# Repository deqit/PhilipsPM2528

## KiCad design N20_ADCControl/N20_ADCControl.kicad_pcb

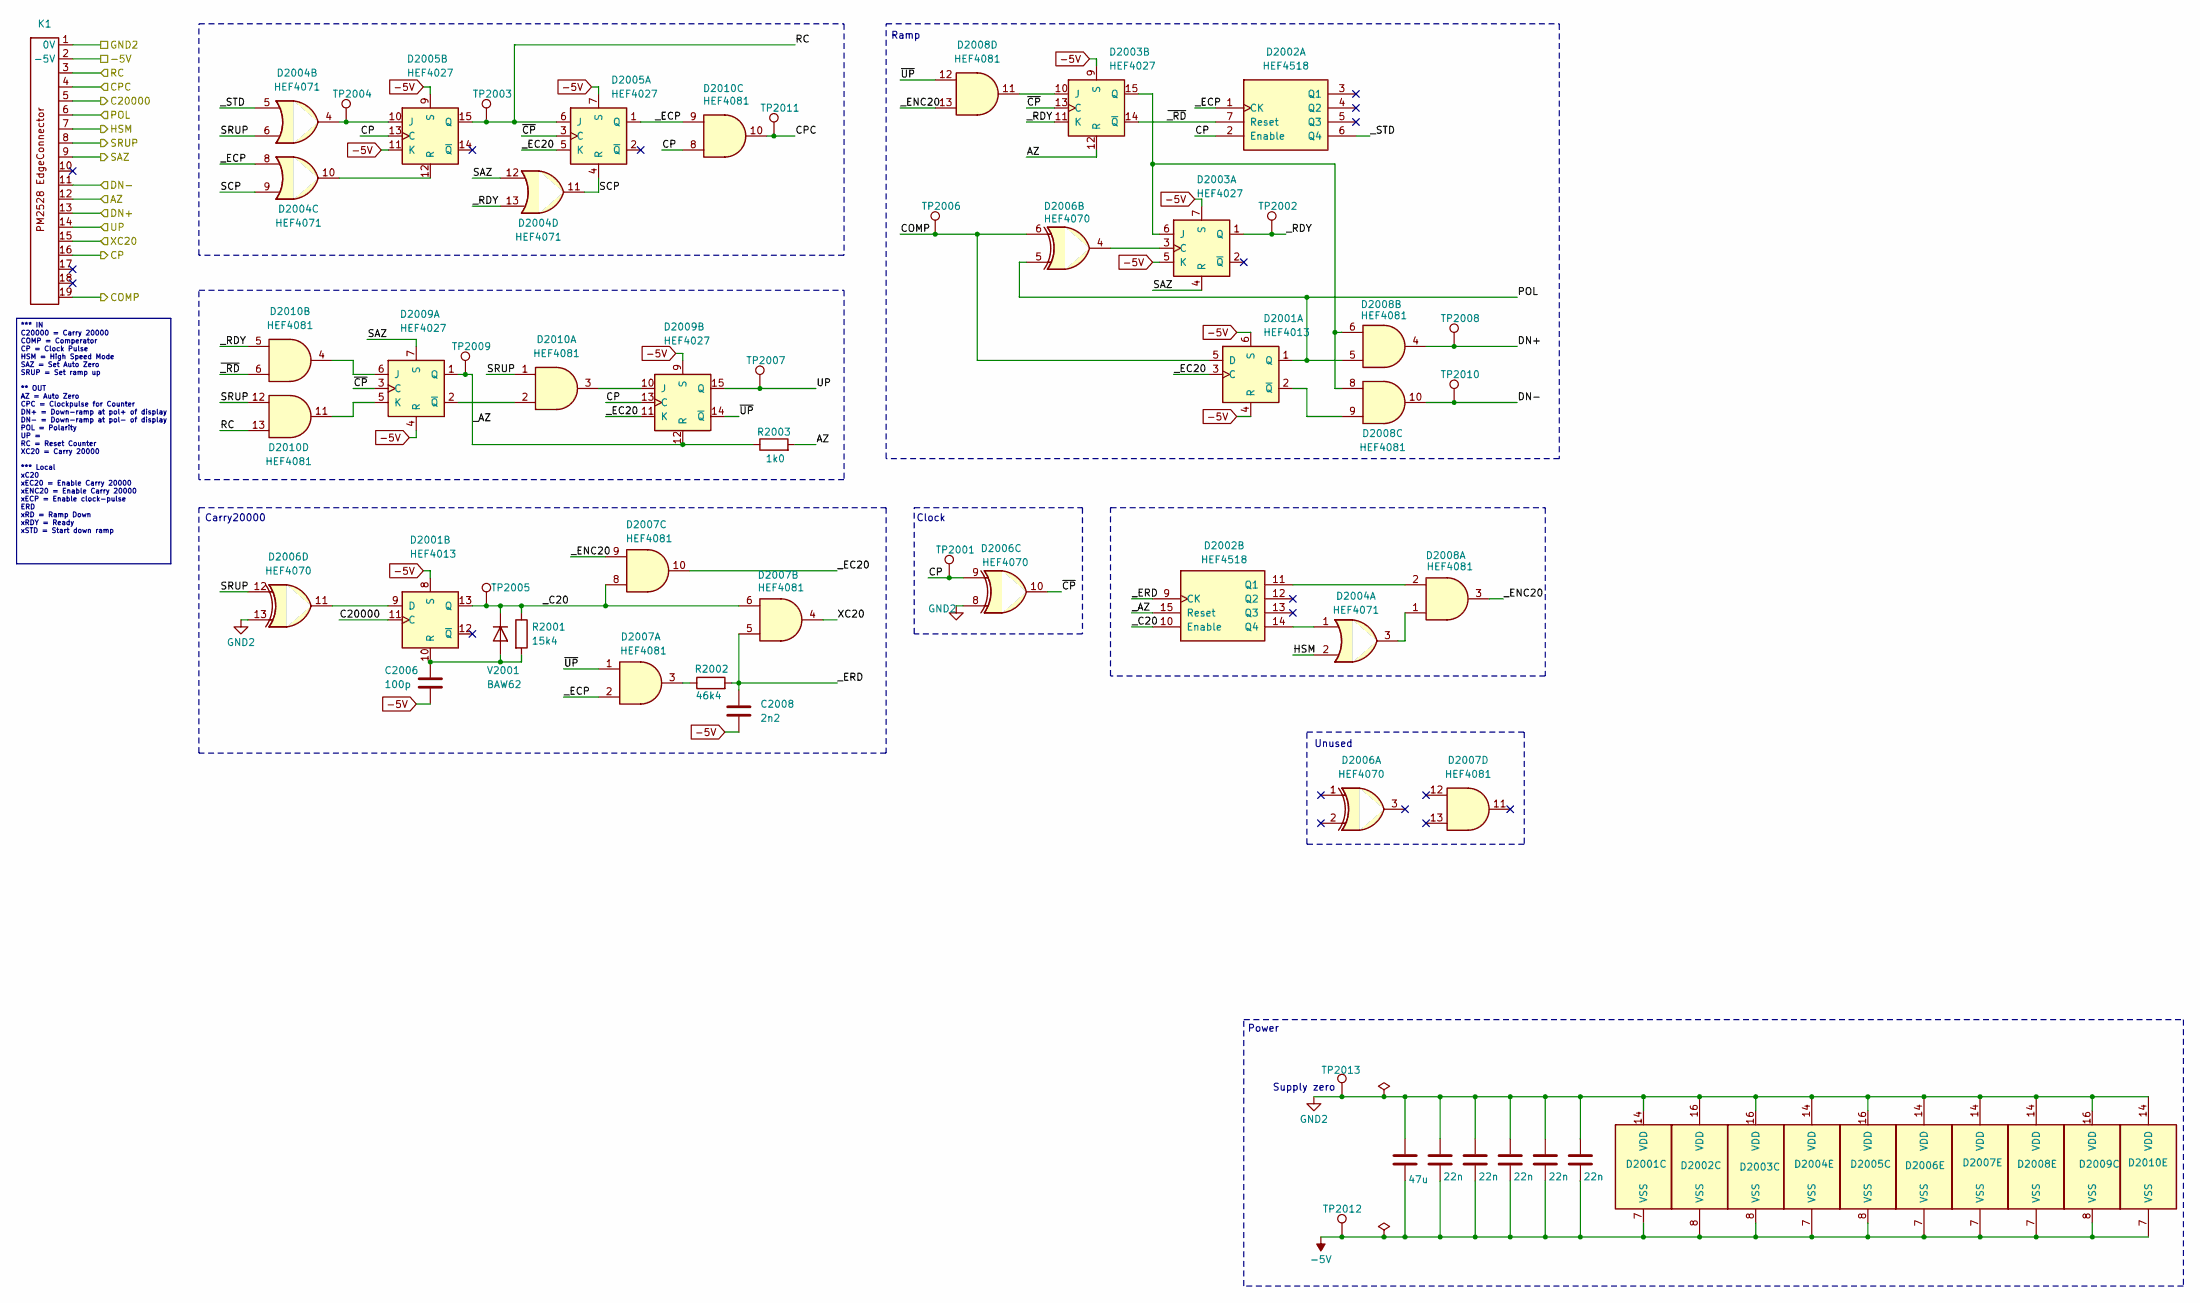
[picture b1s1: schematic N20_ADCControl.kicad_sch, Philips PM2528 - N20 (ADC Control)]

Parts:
C2001, C2002, C2003, C2004, C2005: 22n; C_Rect_L7.0mm_W2.0mm_P5.00mm
C2006: 100p; C_Rect_L7.0mm_W2.0mm_P5.00mm
C2007: 47u; CP_Axial_L10.0mm_D6.0mm_P15.00mm_Horizontal
C2008: 2n2; C_Rect_L7.0mm_W2.0mm_P5.00mm
D2001: HEF4013; DIP-14_W7.62mm
D2002: HEF4518; DIP-16_W7.62mm
D2003, D2005, D2009: HEF4027; DIP-16_W7.62mm
D2004: HEF4071; DIP-14_W7.62mm
D2006: HEF4070; DIP-14_W7.62mm
D2007, D2008, D2010: HEF4081; DIP-14_W7.62mm
K1: PM2528_RiserCardConnector
R2001: 15k4; R_Axial_DIN0207_L6.3mm_D2.5mm_P10.16mm_Horizontal
R2002: 46k4; R_Axial_DIN0207_L6.3mm_D2.5mm_P10.16mm_Horizontal
R2003: 1k0; R_Axial_DIN0207_L6.3mm_D2.5mm_P10.16mm_Horizontal
TP2001, TP2002, TP2003, TP2004, TP2005, TP2006, TP2007, TP2008, TP2009, TP2010, TP2011, TP2012, TP2013: TestPoint; PinHeader_1x01_P1.00mm_Vertical
V2001: BAW62; D_T-1_P10.16mm_Horizontal

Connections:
-5V: C2001.2, C2002.2, C2003.2, C2004.2, C2005.2, C2006.2, C2007.2, C2008.2, D2001.4 (R), D2001.6 (S), D2001.7 (VSS), D2001.8 (S), D2002.8 (VSS), D2003.5 (K), D2003.7 (S), D2003.8 (VSS), D2003.9 (S), D2004.7 (VSS), D2005.7 (S), D2005.8 (VSS), D2005.9 (S), D2005.11 (K), D2006.7 (VSS), D2007.7 (VSS), D2008.7 (VSS), D2009.4 (R), D2009.8 (VSS), D2009.9 (S), D2010.7 (VSS), K1.2 (-5V), TP2012.1
/AZ: D2003.12 (R), K1.12, R2003.2
/C20000: D2001.11 (C), K1.5
/COMP: D2001.5 (D), D2006.6, K1.19, TP2006.1
/CP: D2002.2 (Enable), D2005.13 (C), D2006.9, D2009.13 (C), D2010.8, K1.16, TP2001.1
/CPC: D2010.10, K1.4, TP2011.1
/DN+: D2008.4, K1.13, TP2008.1
/DN-: D2008.10, K1.11, TP2010.1
/HSM: D2004.2, K1.7
/POL: D2001.1 (Q), D2006.5, D2008.5, K1.6
/RC: D2005.6 (J), D2005.15 (Q), D2010.13, K1.3, TP2003.1
/SAZ: D2003.4 (R), D2004.12, D2009.7 (S), K1.9
/SCP: D2004.9, D2004.11, D2005.4 (R)
/SRUP: D2004.6, D2006.12, D2010.1, D2010.12, K1.8
/UP: D2009.15 (Q), K1.14, TP2007.1
/XC20: D2007.4, K1.15
/_AZ: D2002.15 (Reset), D2009.1 (Q), D2009.12 (R), R2003.1, TP2009.1
/_C20: D2001.13 (Q), D2002.10 (Enable), D2007.6, D2007.8, R2001.1, TP2005.1, V2001.1 (K)
/_EC20: D2001.3 (C), D2005.5 (K), D2007.10, D2009.11 (K)
/_ECP: D2002.1 (CK), D2004.8, D2005.1 (Q), D2007.2, D2010.9
/_ENC20: D2007.9, D2008.3, D2008.13
/_ERD: C2008.1, D2002.9 (CK), D2007.5, R2002.2
/_RDY: D2003.1 (Q), D2003.11 (K), D2004.13, D2010.5, TP2002.1
/_STD: D2002.6 (Q4), D2004.5
/~CP: D2003.13 (C), D2005.3 (C), D2006.10, D2009.3 (C)
/~UP: D2007.1, D2008.12, D2009.14 (~Q)
/~_RD: D2002.7 (Reset), D2003.14 (~Q), D2010.6
GND2: C2001.1, C2002.1, C2003.1, C2004.1, C2005.1, C2007.1, D2001.14 (VDD), D2002.16 (VDD), D2003.16 (VDD), D2004.14 (VDD), D2005.16 (VDD), D2006.8, D2006.13, D2006.14 (VDD), D2007.14 (VDD), D2008.14 (VDD), D2009.16 (VDD), D2010.14 (VDD), K1.1 (0V), TP2013.1
unnamed: D2001.2 (~Q), D2008.9
unnamed: D2001.9 (D), D2006.11
unnamed: C2006.1, D2001.10 (R), R2001.2, V2001.2 (A)
unnamed: D2002.11 (Q1), D2008.2
unnamed: D2002.14 (Q4), D2004.1
unnamed: D2003.3 (C), D2006.4
unnamed: D2003.6 (J), D2003.15 (Q), D2008.6, D2008.8
unnamed: D2003.10 (J), D2008.11
unnamed: D2004.3, D2008.1
unnamed: D2004.4, D2005.10 (J), TP2004.1
unnamed: D2004.10, D2005.12 (R)
unnamed: D2007.3, R2002.1
unnamed: D2009.6 (J), D2010.4
unnamed: D2009.5 (K), D2010.11
unnamed: D2009.2 (~Q), D2010.2
unnamed: D2009.10 (J), D2010.3

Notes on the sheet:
Ramp
Power
Supply zero
Clock
Carry20000
Unused
*** IN C20000 = Carry 20000 COMP = Comperator CP = Clock Pulse HSM = High Speed Mode SAZ = Set Auto Zero SRUP = Set ramp up ** OUT AZ = Auto Zero CPC = Clockpulse for Counter DN+ = Down-ramp at pol+ of display DN- = Down-ramp at pol- of display POL = Polarity UP = RC = Reset Counter XC20 = Carry 20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

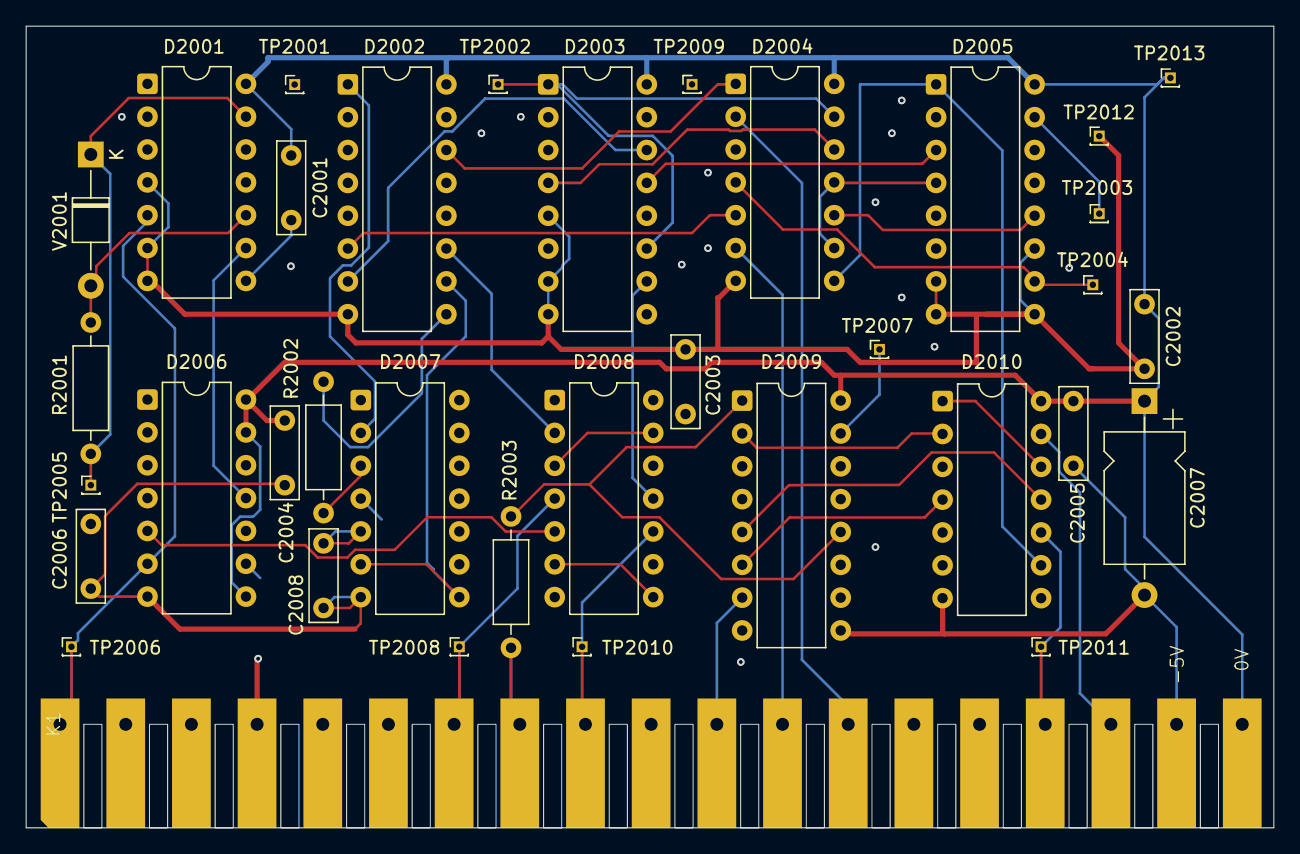
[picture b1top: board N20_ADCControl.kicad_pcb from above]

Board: 2 copper layers, 96.5 x 62.0 mm, 36 parts (0 on the bottom side), 44 nets.

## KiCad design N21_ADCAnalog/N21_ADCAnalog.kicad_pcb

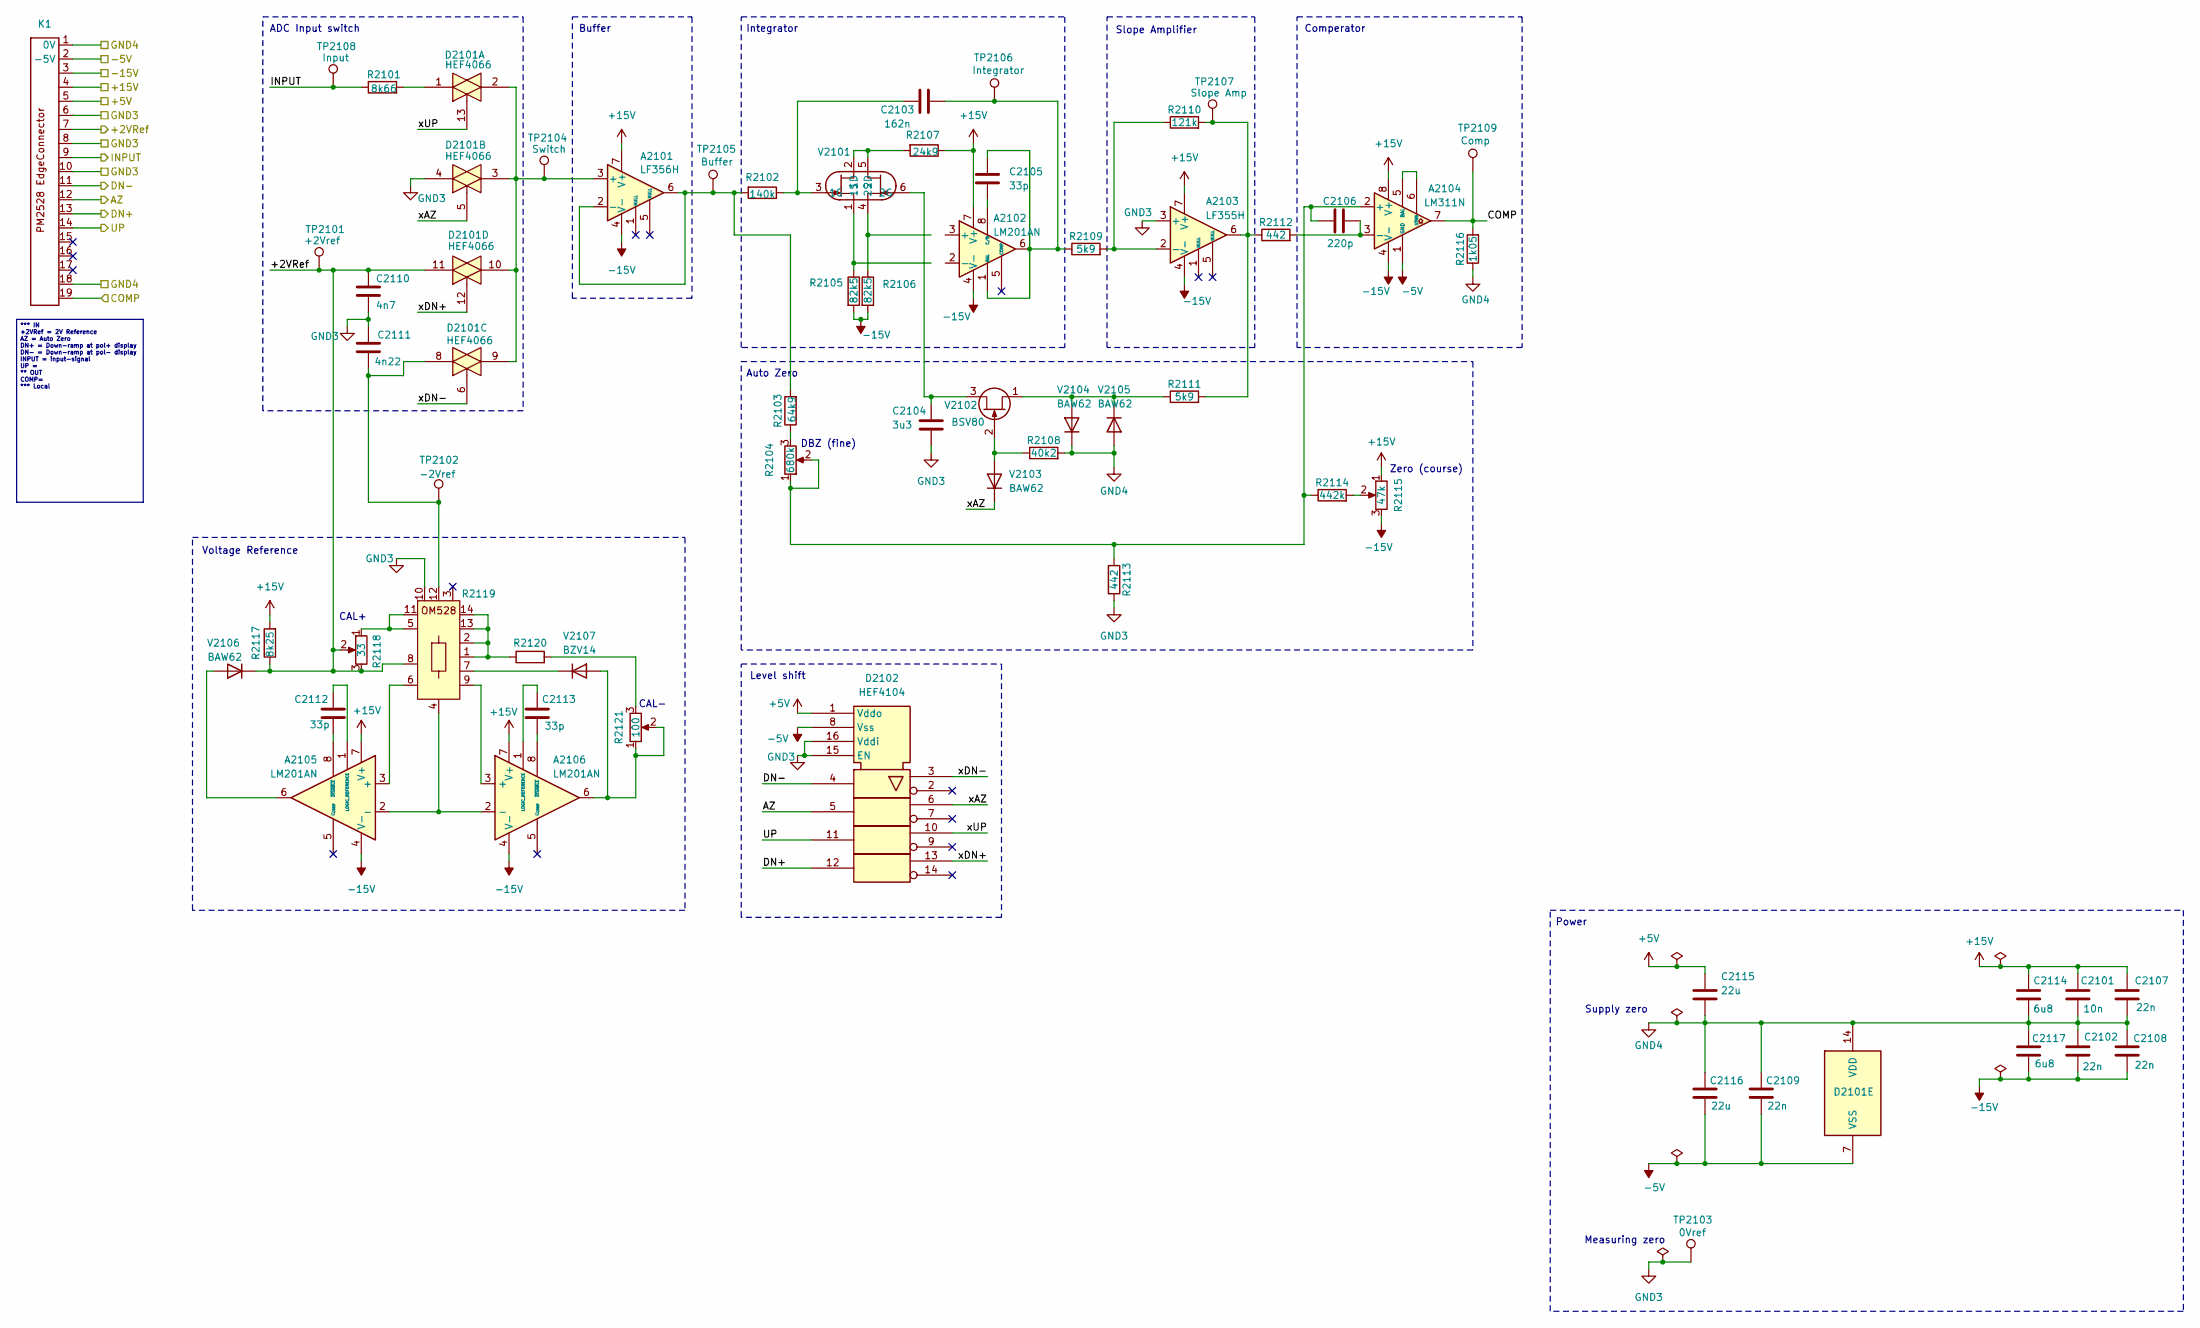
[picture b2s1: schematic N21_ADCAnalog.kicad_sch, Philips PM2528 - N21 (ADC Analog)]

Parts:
A2101: LF356H; DIP-8_W7.62mm
A2102, A2105, A2106: LM201AN; DIP-8_W7.62mm
A2103: LF355H; DIP-8_W7.62mm
A2104: LM311N
C2101: 10n; C_Disc_D4.3mm_W1.9mm_P5.00mm
C2102, C2107, C2108, C2109: 22n; C_Disc_D4.3mm_W1.9mm_P5.00mm
C2103: 162n; CP_Axial_L25.0mm_D10.0mm_P30.00mm_Horizontal
C2104: 3u3; C_Rect_L26.5mm_W8.5mm_P22.50mm_MKS4
C2105, C2112, C2113: 33p; C_Disc_D4.3mm_W1.9mm_P5.00mm
C2106: 220p; C_Disc_D4.3mm_W1.9mm_P5.00mm
C2110: 4n7; C_Disc_D4.3mm_W1.9mm_P5.00mm
C2111: 4n22
C2114, C2117: 6u8; C_Disc_D5.0mm_W2.5mm_P5.00mm
C2115, C2116: 22u; C_Disc_D5.0mm_W2.5mm_P5.00mm
D2101: HEF4066; DIP-14_W7.62mm
D2102: HEF4104; DIP-16_W7.62mm
K1: PM2528_RiserCardConnector
R2101: 8k66; R_Axial_DIN0207_L6.3mm_D2.5mm_P10.16mm_Horizontal
R2102: 140k; R_Axial_DIN0207_L6.3mm_D2.5mm_P10.16mm_Horizontal
R2103: 64k9; R_Axial_DIN0207_L6.3mm_D2.5mm_P10.16mm_Horizontal
R2104: 680k; Potentiometer horizontal ceramic
R2105, R2106: 82k5; R_Axial_DIN0207_L6.3mm_D2.5mm_P10.16mm_Horizontal
R2107: 24k9; R_Axial_DIN0207_L6.3mm_D2.5mm_P10.16mm_Horizontal
R2108: 40k2; R_Axial_DIN0207_L6.3mm_D2.5mm_P10.16mm_Horizontal
R2109, R2111: 5k9; R_Axial_DIN0207_L6.3mm_D2.5mm_P10.16mm_Horizontal
R2110: 121k; R_Axial_DIN0207_L6.3mm_D2.5mm_P10.16mm_Horizontal
R2112, R2113: 442; R_Axial_DIN0207_L6.3mm_D2.5mm_P10.16mm_Horizontal
R2114: 442k; R_Axial_DIN0207_L6.3mm_D2.5mm_P10.16mm_Horizontal
R2115: 47k; Potentiometer horizontal ceramic
R2116: 1k05; R_Axial_DIN0207_L6.3mm_D2.5mm_P10.16mm_Horizontal
R2117: 8k25; R_Axial_DIN0207_L6.3mm_D2.5mm_P10.16mm_Horizontal
R2118: 33; Potentiometer horizontal ceramic
R2119: DIP-14_W7.62mm_Socket
R2120: (no value)
R2121: 100; Potentiometer horizontal ceramic
TP2101: +2Vref; Pin_D1.0mm_L10.0mm
TP2102: -2Vref; Pin_D1.0mm_L10.0mm
TP2103: 0Vref; Pin_D1.0mm_L10.0mm
TP2104: Switch; Pin_D1.0mm_L10.0mm
TP2105: Buffer; Pin_D1.0mm_L10.0mm
TP2106: Integrator; Pin_D1.0mm_L10.0mm
TP2107: Slope Amp; Pin_D1.0mm_L10.0mm
TP2108: Input; Pin_D1.0mm_L10.0mm
TP2109: Comp; Pin_D1.0mm_L10.0mm
V2101: (no value)
V2102: BSV80; TO-92_Inline
V2103, V2104, V2105, V2106: BAW62; D_DO-34_SOD68_P10.16mm_Horizontal
V2107: BZV14; D_DO-34_SOD68_P10.16mm_Horizontal

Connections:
+5V: C2115.1, D2102.1 (Vddo), K1.5
+15V: A2101.7 (V+), A2102.7 (V+), A2103.7 (V+), A2104.8 (V+), A2105.7 (V+), A2106.7 (V+), C2101.2, C2107.1, C2114.1, K1.4, R2107.1, R2115.1, R2117.2
-5V: A2104.1 (GND), C2109.2, C2116.2, D2101.7 (VSS), D2102.8 (Vss), K1.2 (-5V)
-15V: A2101.4 (V-), A2102.4 (V-), A2103.4 (V-), A2104.4 (V-), A2105.4 (V-), A2106.4 (V-), C2102.2, C2108.2, C2117.2, K1.3, R2105.2, R2106.2, R2115.3
/+2VRef: C2110.2, D2101.11, K1.7, R2117.1, R2118.2, R2118.3, R2119.8, TP2101.1, V2106.1 (K)
/AZ: D2102.5, K1.12
/COMP: A2104.7, K1.19, R2116.2, TP2109.1
/DN+: D2102.12, K1.13
/DN-: D2102.4, K1.11
/INPUT: K1.9, R2101.1, TP2108.1
/UP: D2102.11, K1.14
/xAZ: D2101.5, D2102.6, V2103.1 (K)
/xDN+: D2101.12, D2102.13
/xDN-: D2101.6, D2102.3
/xUP: D2101.13, D2102.10
GND3: A2103.3 (+), C2104.2, C2110.1, C2111.2, D2101.4, D2102.15 (EN), D2102.16 (Vddi), K1.6, K1.8, K1.10, R2113.2, R2119.10, TP2103.1
GND4: C2101.1, C2102.1, C2107.2, C2108.1, C2109.1, C2114.2, C2115.2, C2116.1, C2117.1, D2101.14 (VDD), K1.1 (0V), K1.18, R2108.2, R2116.1, V2104.1 (K), V2105.2 (A)
unnamed: A2101.3 (+), D2101.2, D2101.3, D2101.9, D2101.10, TP2104.1
unnamed: A2101.2 (-), A2101.6, R2102.2, R2103.2, TP2105.1
unnamed: A2102.1 (BAL), A2102.6, C2103.1, C2105.1, R2109.1, TP2106.1
unnamed: A2102.8 (C/B), C2105.2
unnamed: A2103.2 (-), R2109.2, R2110.1
unnamed: A2103.6, R2110.2, R2111.2, R2112.1, TP2107.1
unnamed: A2104.2 (+), C2106.2, R2104.1, R2104.2, R2113.1, R2114.1
unnamed: A2104.3 (-), C2106.1, R2112.2
unnamed: A2104.5 (BAL), A2104.6 (STRB)
unnamed: A2105.3 (+), R2119.6
unnamed: A2105.2 (-), A2106.2 (-), R2119.4
unnamed: A2105.1 (LOGIC_REFERENCE), C2112.2
unnamed: A2105.8 (~DISABLE), C2112.1
unnamed: A2106.3 (+), R2119.9
unnamed: A2106.1 (LOGIC_REFERENCE), C2113.2
unnamed: A2106.8 (~DISABLE), C2113.1
unnamed: C2111.1, D2101.8, R2119.12, TP2102.1
unnamed: D2101.1, R2101.2
unnamed: R2103.1, R2104.3
unnamed: R2114.2, R2115.2
unnamed: R2118.1, R2119.5, R2119.11
unnamed: R2119.1, R2119.2, R2119.13, R2119.14, R2120.1
unnamed: R2120.2, R2121.3
unnamed: R2107.2, V2101.2 (1D), V2101.5 (2D)
unnamed: C2103.2, R2102.1, V2101.3 (1G)
unnamed: R2105.1, V2101.1 (1S)
unnamed: C2104.1, V2101.6 (2G), V2102.3 (S)
unnamed: R2106.1, V2101.4 (2S)
unnamed: R2111.1, V2102.1 (D), V2104.2 (A), V2105.1 (K)
unnamed: R2108.1, V2102.2 (G), V2103.2 (A)
unnamed: A2105.6, V2106.2 (A)
unnamed: A2106.6, R2121.1, R2121.2, V2107.2 (A)
unnamed: R2119.7, V2107.1 (K)

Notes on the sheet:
Supply zero
CAL+
Buffer
Power
Comperator
Voltage Reference
Integrator
DBZ (fine)
Measuring zero
Slope Amplifier
Zero (course)
Auto Zero
Level shift
CAL-
ADC Input switch
*** IN +2VRef = 2V Reference AZ = Auto Zero DN+ = Down-ramp at pol+ display DN- = Down-ramp at pol- display INPUT = input-signal UP = ** OUT COMP= *** Local

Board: 2 copper layers, 60 parts (0 on the bottom side), 46 nets, no tracks yet.

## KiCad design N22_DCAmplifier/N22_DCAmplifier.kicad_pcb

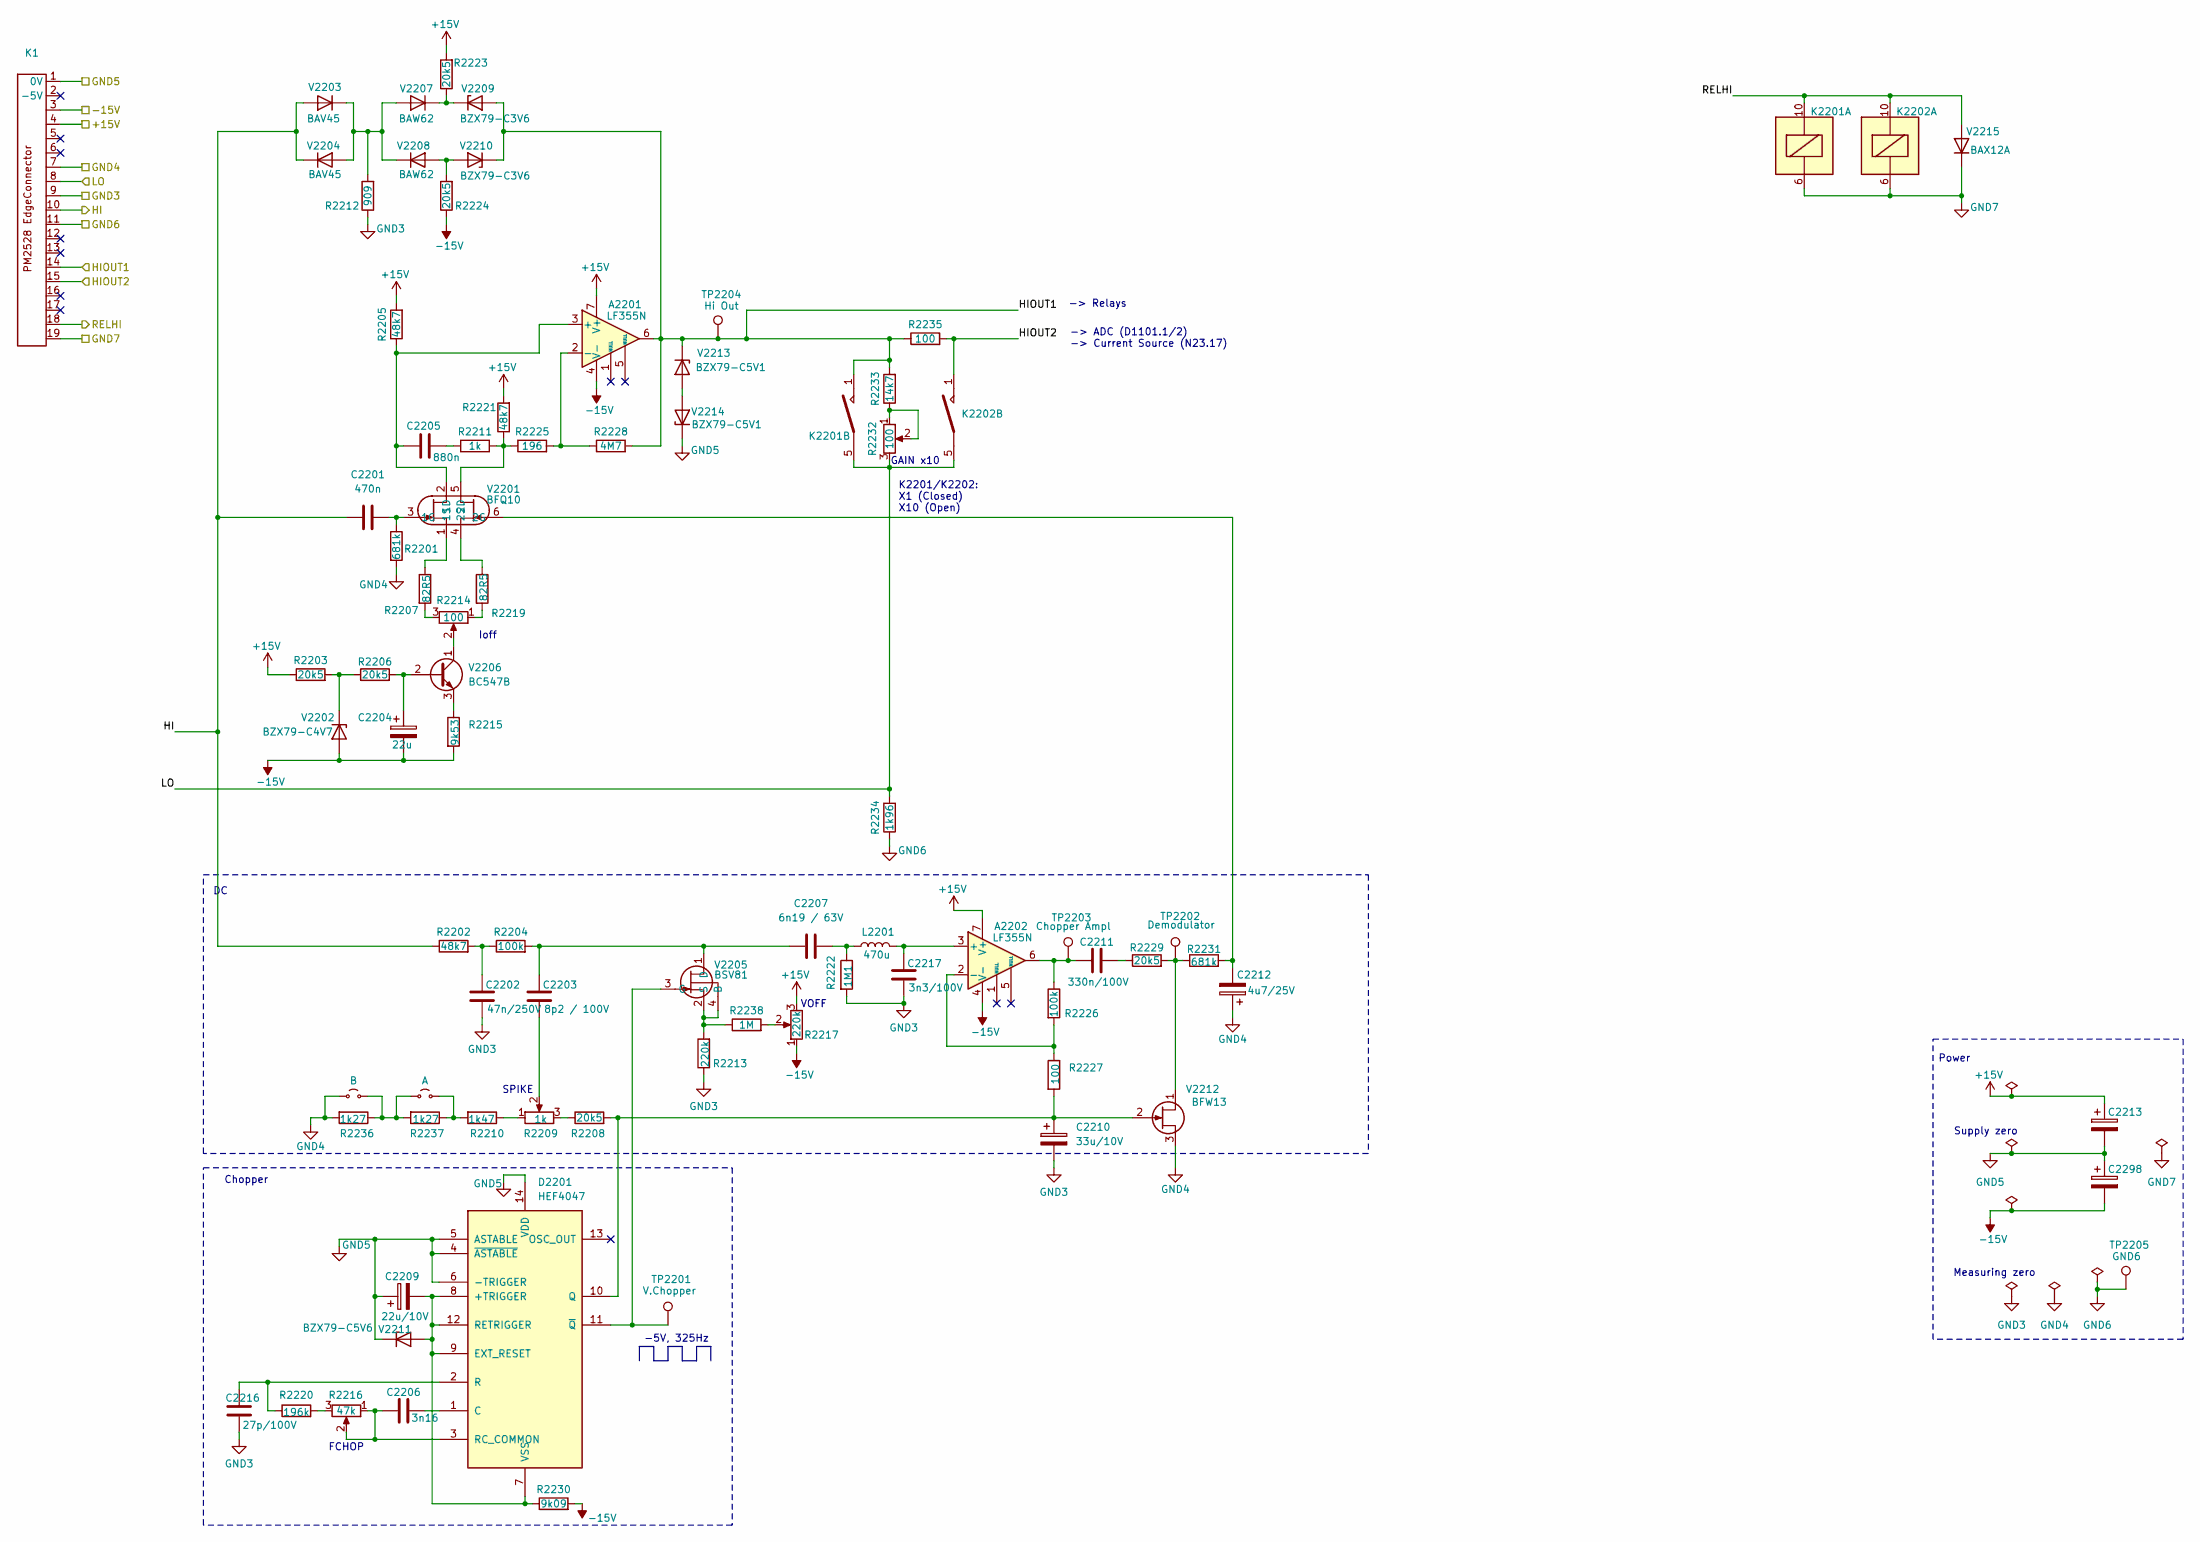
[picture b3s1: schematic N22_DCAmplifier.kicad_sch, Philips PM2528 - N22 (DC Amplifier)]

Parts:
A2201, A2202: LF355N; DIP-8_W7.62mm
C2201: 470n; C_Rect_L18.0mm_W6.0mm_P15.00mm_FKS3_FKP3
C2202: 47n/250V; C_Rect_L10.0mm_W4.0mm_P7.50mm_FKS3_FKP3
C2203: 8p2 / 100V; C_Disc_D4.3mm_W1.9mm_P5.00mm
C2204: 22u; CP_Radial_Tantal_D4.5mm_P5.00mm
C2205: 880n; C_Rect_L18.0mm_W5.0mm_P15.00mm_FKS3_FKP3
C2206: 3n16; C_Axial_L3.8mm_D2.6mm_P15.00mm_Horizontal
C2207: 6n19 / 63V; C_Axial_L3.8mm_D2.6mm_P15.00mm_Horizontal
C2209: 22u/10V; C_Disc_D5.0mm_W2.5mm_P5.00mm
C2210: 33u/10V; CP_Radial_Tantal_D4.5mm_P5.00mm
C2211: 330n/100V; C_Rect_L18.0mm_W5.0mm_P15.00mm_FKS3_FKP3
C2212: 4u7/25V; CP_Radial_Tantal_D4.5mm_P5.00mm
C2213, C2298: C_Polarized; C_Disc_D4.7mm_W2.5mm_P5.00mm
C2216: 27p/100V; C_Disc_D5.1mm_W3.2mm_P5.00mm
C2217: 3n3/100V; C_Disc_D4.3mm_W1.9mm_P5.00mm
D2201: HEF4047; DIP-14_W7.62mm
JP1: B; TestPoint_Bridge_Pitch2.54mm_Drill1.0mm
JP2: A; TestPoint_Bridge_Pitch2.54mm_Drill1.0mm
K1: PM2528_RiserCardConnector
K2201, K2202: Reed relay assy
L2201: 470u; L_Axial_L9.5mm_D4.0mm_P15.24mm_Horizontal_Fastron_SMCC
R2201, R2231: 681k; R_Axial_DIN0207_L6.3mm_D2.5mm_P10.16mm_Horizontal
R2202, R2205, R2221: 48k7; R_Axial_DIN0207_L6.3mm_D2.5mm_P10.16mm_Horizontal
R2203, R2206, R2208, R2223, R2224, R2229: 20k5; R_Axial_DIN0207_L6.3mm_D2.5mm_P10.16mm_Horizontal
R2204, R2226: 100k; R_Axial_DIN0207_L6.3mm_D2.5mm_P10.16mm_Horizontal
R2207, R2219: 82R5; R_Axial_DIN0207_L6.3mm_D2.5mm_P10.16mm_Horizontal
R2209: 1k; Potentiometer horizontal ceramic
R2210: 1k47; R_Axial_DIN0207_L6.3mm_D2.5mm_P10.16mm_Horizontal
R2211: 1k; R_Axial_DIN0207_L6.3mm_D2.5mm_P10.16mm_Horizontal
R2212: 909; R_Axial_DIN0207_L6.3mm_D2.5mm_P10.16mm_Horizontal
R2213: 220k; R_Axial_DIN0207_L6.3mm_D2.5mm_P10.16mm_Horizontal
R2214, R2232: 100; Potentiometer horizontal ceramic
R2215: 9k53; R_Axial_DIN0207_L6.3mm_D2.5mm_P10.16mm_Horizontal
R2216: 47k; Potentiometer horizontal ceramic
R2217: 220k; Potentiometer horizontal ceramic
R2220: 196k; R_Axial_DIN0207_L6.3mm_D2.5mm_P10.16mm_Horizontal
R2222: 1M1; R_Axial_DIN0207_L6.3mm_D2.5mm_P10.16mm_Horizontal
R2225: 196; R_Axial_DIN0207_L6.3mm_D2.5mm_P10.16mm_Horizontal
R2227, R2235: 100; R_Axial_DIN0207_L6.3mm_D2.5mm_P10.16mm_Horizontal
R2228: 4M7; R_Axial_DIN0207_L6.3mm_D2.5mm_P10.16mm_Horizontal
R2230: 9k09; R_Axial_DIN0207_L6.3mm_D2.5mm_P10.16mm_Horizontal
R2233: 14k7; R_Axial_DIN0207_L6.3mm_D2.5mm_P10.16mm_Horizontal
R2234: 1k96; R_Axial_DIN0207_L6.3mm_D2.5mm_P10.16mm_Horizontal
R2236, R2237: 1k27; R_Axial_DIN0207_L6.3mm_D2.5mm_P10.16mm_Horizontal
R2238: 1M; R_Axial_DIN0309_L9.0mm_D3.2mm_P12.70mm_Horizontal
TP2201: V.Chopper; Pin_D0.9mm_L10.0mm_W2.4mm_FlatFork
TP2202: Demodulator; Pin_D0.9mm_L10.0mm_W2.4mm_FlatFork
TP2203: Chopper Ampl; Pin_D0.9mm_L10.0mm_W2.4mm_FlatFork
TP2204: Hi Out; Pin_D0.9mm_L10.0mm_W2.4mm_FlatFork
TP2205: GND6; Pin_D0.9mm_L10.0mm_W2.4mm_FlatFork
V2201: BFQ10; TO-75-6
V2202: BZX79-C4V7; D_DO-35_SOD27_P10.16mm_Horizontal
V2203, V2204: BAV45; D_DO-35_SOD27_P5.08mm_Vertical_AnodeUp
V2205: BSV81; TO-72-4
V2206: BC547B; TO-92_Inline
V2207, V2208: BAW62; D_DO-35_SOD27_P10.16mm_Horizontal
V2209, V2210: BZX79-C3V6; D_DO-35_SOD27_P10.16mm_Horizontal
V2211: BZX79-C5V6; D_DO-35_SOD27_P10.16mm_Horizontal
V2212: BFW13; TO-72-4
V2213, V2214: BZX79-C5V1; D_DO-35_SOD27_P12.70mm_Horizontal
V2215: BAX12A; D_DO-35_SOD27_P10.16mm_Horizontal

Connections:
+15V: A2201.7 (V+), A2202.7 (V+), C2213.1, K1.4, R2203.1, R2205.2, R2217.3, R2221.2, R2223.2
-15V: A2201.4 (V-), A2202.4 (V-), C2204.2, C2298.2, K1.3, R2215.2, R2217.1, R2224.1, R2230.2, V2202.2 (A)
/HI: C2201.1, K1.10, R2202.1, V2203.2 (A), V2204.1 (K)
/HIOUT1: A2201.6, K1.14, K2201.1, R2228.2, R2233.2, R2235.1, TP2204.1, V2209.2 (A), V2210.1 (K), V2213.1 (K)
/HIOUT2: K1.15, K2202.1, R2235.2
/LO: K1.8, K2201.5, K2202.5, R2232.3, R2234.2
/RELHI: K1.18, K2201.10, K2202.10, V2215.2 (A)
GND3: C2202.1, C2210.2, C2216.1, C2217.1, K1.9, R2212.1, R2213.1, R2222.2
GND4: C2212.1, JP1.1 (A), K1.7, R2201.2, R2236.2, V2212.3 (S)
GND5: C2209.1, C2213.2, C2298.1, D2201.4 (~ASTABLE), D2201.5 (ASTABLE), D2201.6 (-TRIGGER), D2201.14 (VDD), K1.1 (0V), V2211.1 (K), V2214.1 (K)
GND6: K1.11, R2234.1, TP2205.1
GND7: K1.19, K2201.6, K2202.6, V2215.1 (K)
unnamed: A2201.3 (+), C2205.1, R2205.1, V2201.2 (1D)
unnamed: A2201.2 (-), R2225.2, R2228.1
unnamed: A2202.3 (+), C2217.2, L2201.2
unnamed: A2202.2 (-), R2226.2, R2227.1
unnamed: A2202.6, C2211.1, R2226.1, TP2203.1
unnamed: C2202.2, R2202.2, R2204.1
unnamed: C2203.1, R2209.2
unnamed: C2205.2, R2211.1
unnamed: C2207.2, L2201.1, R2222.1
unnamed: C2211.2, R2229.1
unnamed: C2209.2, D2201.7 (VSS), D2201.8 (+TRIGGER), D2201.9 (EXT_RESET), D2201.12 (RETRIGGER), R2230.1, V2211.2 (A)
unnamed: C2206.2, D2201.1 (C)
unnamed: C2210.1, D2201.10 (Q), R2208.2, R2227.2, V2212.2 (G)
unnamed: C2216.2, D2201.2 (R), R2220.1
unnamed: C2206.1, D2201.3 (RC_COMMON), R2216.1, R2216.2
unnamed: D2201.11 (~Q), TP2201.1, V2205.3 (G)
unnamed: JP1.2 (B), JP2.1 (A), R2236.1, R2237.2
unnamed: JP2.2 (B), R2210.2, R2237.1
unnamed: R2207.2, R2214.3
unnamed: R2208.1, R2209.3
unnamed: R2209.1, R2210.1
unnamed: R2214.1, R2219.2
unnamed: R2216.3, R2220.2
unnamed: R2217.2, R2238.2
unnamed: R2232.1, R2232.2, R2233.1
unnamed: C2201.2, R2201.1, V2201.3 (1G)
unnamed: R2207.1, V2201.1 (1S)
unnamed: R2211.2, R2221.1, R2225.1, V2201.5 (2D)
unnamed: C2212.2, R2231.2, V2201.6 (2G)
unnamed: R2219.1, V2201.4 (2S)
unnamed: R2203.2, R2206.1, V2202.1 (K)
unnamed: R2212.2, V2203.1 (K), V2204.2 (A), V2207.2 (A), V2208.1 (K)
unnamed: R2213.2, R2238.1, V2205.2 (S), V2205.4 (B)
unnamed: C2203.2, C2207.1, R2204.2, V2205.1 (D)
unnamed: C2204.1, R2206.2, V2206.2 (B)
unnamed: R2214.2, V2206.1 (C)
unnamed: R2215.1, V2206.3 (E)
unnamed: R2223.1, V2207.1 (K), V2209.1 (K)
unnamed: R2224.2, V2208.2 (A), V2210.2 (A)
unnamed: R2229.2, R2231.1, TP2202.1, V2212.1 (D)
unnamed: V2213.2 (A), V2214.2 (A)

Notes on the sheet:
-> Relays
-> ADC (D1101.1/2) -> Current Source (N23.17)
FCHOP
SPIKE
Supply zero
GAIN x10
K2201/K2202: X1 (Closed) X10 (Open)
VOFF
Chopper
-5V, 325Hz
Power
Measuring zero
Ioff

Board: 2 copper layers, 81 parts (0 on the bottom side), 53 nets, no tracks yet.
